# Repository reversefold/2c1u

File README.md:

# 2c1u - Two computers, one USB port

The name is a riff on 2p1c, a shorthand for "Two players, one controller", a fun challenge that some speedrunners enjoy.

This project has software and hardware designs which form a USB switch, allowing for automatically moving a USB device between two computers, either through pressing of a hardware button or controlled via software running on the computers. If you plug a USB hub into the port that is switched you can switch, for instance, a keyboard and mouse between two computers, as if you were using software like Synergy.

## Layout
* 2c1u_kicad - KiCAD files for the hardware of the project, including a PCB layout.
* CircuitPy_Adafruit - Software for the Raspberry Pi devices that the hardware uses.
* 2c1u, pyproject.toml, pdm.lock - These constitute the computer software which communicate to the hardware over USB-Serial.

## Hardware
Required hardware:
* 2x [Adafruit Feather RP2040](https://www.adafruit.com/product/4884)
* 2x [TinkerBoy USB 2.0 Hub Breakout](https://www.tinkerboy.xyz/product/tinkerboy-usb-hub-4-port-usb-hub-2-0/)
* 3x [Adafruit 4090 - USB-C Breakout](https://www.adafruit.com/product/4090)
* 2x [Omron G6SK-2-DC5 relays](https://www.mouser.com/ProductDetail/Omron-Electronics/G6SK-2-DC5?qs=Mrnyg3lK62HQss%2FMQAyqbw%3D%3D)
* 2x [PN2222A Transistor](https://www.digikey.com/en/products/detail/nte-electronics-inc/PN2222A/11655004)
* 2x [Tactile Button Switch](https://www.adafruit.com/product/367)
* 1x [Sparkfun Cherry MX Switch Breakout](https://www.sparkfun.com/products/13773)
* 1x Cherry MX Compatible Switch
* 1x Keycap
* 2x 1K resistors
* 2x 10K resistors

I am also using several feather breakout boards for additional output as I had them around to play with:
* 1x [NeoPixel FeatherWing](https://www.adafruit.com/product/2945)
* 1x [Adafruit FeatherWing OLED - 128x64](https://www.adafruit.com/product/4650)
* 1x [FeatherWing Tripler Mini Kit](https://www.adafruit.com/product/3417)

You will additionally need PCB mount headers for the various components and either breadboards or a custom PCB (see fully functional PCB in `2c1u_kicad`). Note that the TinkerBoy USB 2.0 Hub Breakout boards are not breadboard compatible, the holes are not uniformly separated and require some creativity to hook up with a breadboard.

All of the soldering for the PCB are through-hole, as are nearly all of the boards. The one exception is the two data pads on the RP2040 boards. These pads connect to the 2 data pins of the USB connector so they can be used to wire up the RP2040 to the TinkerBoy boards as a USB device.

The Raspberry Pi boards are the brains of the switch. Each one connects to one of the computers as a USB serial device as a control channel. The primary one also controls the relays which switch the USB devices between the two computers.

One USB connector is for the input device to switch between the two hosts. I use a simple USB hub and plug both my keyboard and mouse into it, then plug the hub into the switch. The other 2 USB connectors connect to the two host computers. The TinkerBoy boards act as USB hubs, allowing both the RPi boards and the input devices to be connected via one USB connection. Note that this switch supports USB 2.0 only, so it's only really useful for lower bandwidth devices, like HID devices.

The Cherry MX switch allows switching between the two host computers manually. The two small switch buttons next to the USB connectors on the PCB can be held down while plugging in the associated USB cable to have the RPi start up in developer mode, with a repl usb-serial connection and as usb mass storage.

## Device-side software
The device-side software is written in Python for CircuitPy running on an Adafruit device. For the secondary create a file named `secondary` in the root of the drive.

The `boot.py` file turns on the data interface and turns off the repl interface, as well as turns off the ability of the CircuitPy device to be a USB drive. If you want access to the USB drive and repl interface you can pull pin D5 up (the buttons next to the USB connectors on the PCB are for this).

## Computer-side software
The computer-side software is written in Python and uses pdm for dependency management. Once you've installed pdm, change to the project directory, use the command `pdm install` to have pdm install all of the dependencies, then use the command `pdm run python 2c1u/main.py` to start the software. Until you have the right hardware hooked up it will loop with exceptions about not finding the serial interface.

The code near the top that defines `X_EDGE` configures how the edge of the screen is detected for the two machines, one Windows on the right, and one not Windows on the left.

## History

This project is the culmination of years of thinking and tinkering in my free time. For a long time, I have used projects such as x2vnc and Synergy to have the mouse and keyboard of one computer move to another computer's screen over the network, allowing for easy use of multiple computers with their own screens with a single keyboard and mouse. When I started working from home more often I wanted a way to switch between my personal and work computers seamlessly. Synergy did just that for me for a while but there were always caveats. Slowdown on the computers and random network errors would cause the input to lag or disconnect.

When my work computer was forced to have a full tunnel VPN the fully software-based network solution just wouldn't work reliably any more. The classic solution to this was a KVM, a hardware switch meant to move a keyboard, video, and mouse from one computer to another. I had no need for the video part of this, however, and I had trouble finding anything which could be software controlled. I wanted to mimic what I could do with Synergy, moving my mouse to one side of the monitor and have my mouse and keyboard move seamlessly to the other computer's monitor next to it.

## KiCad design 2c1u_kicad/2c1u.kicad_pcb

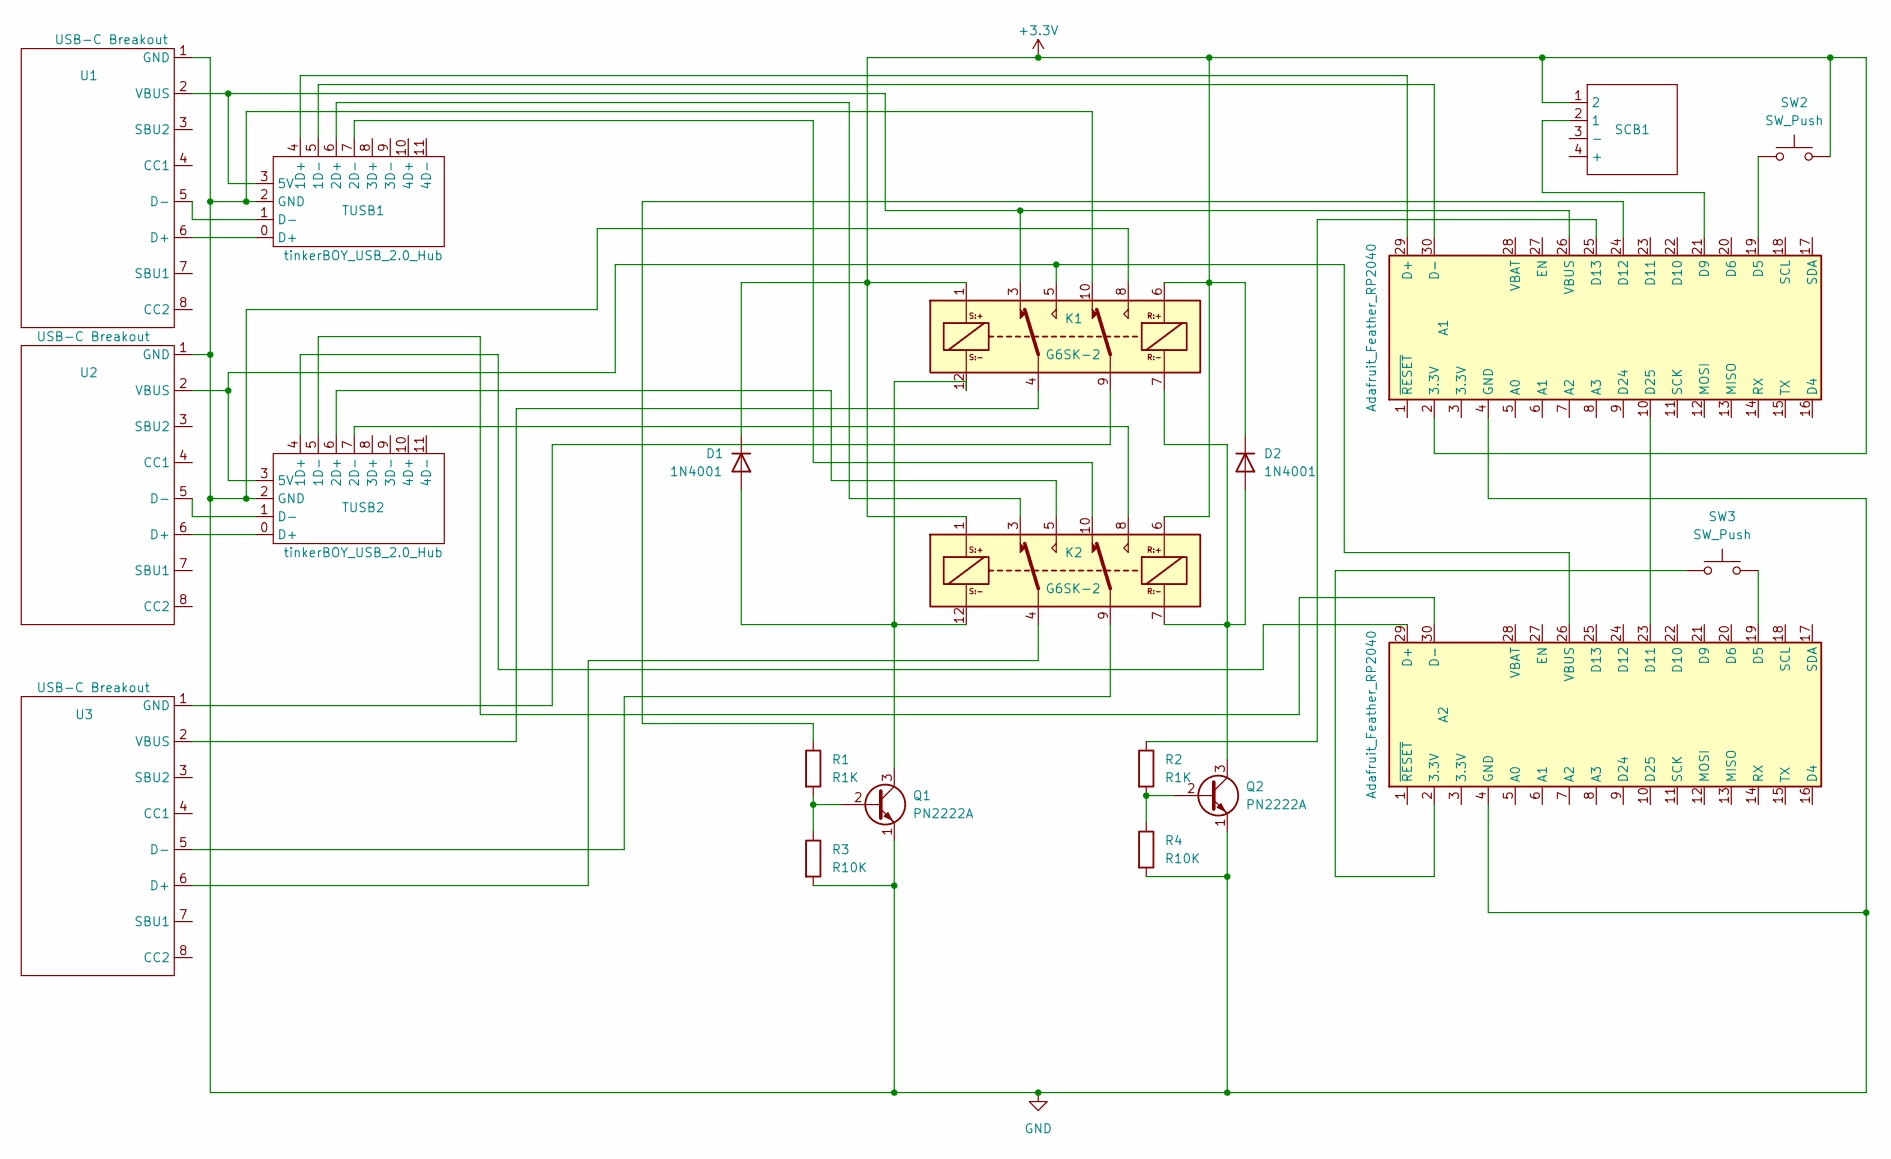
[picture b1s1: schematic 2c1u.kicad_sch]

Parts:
A1, A2: Adafruit_Feather_RP2040; Adafruit Feather RP2040
D1, D2: 1N4001; D_DO-41_SOD81_P10.16mm_Horizontal
K1, K2: G6SK-2; Relay_DPDT_Omron_G6SK-2
Q1, Q2: PN2222A; TO-92_Inline
R1, R2: R1K; R_Axial_DIN0204_L3.6mm_D1.6mm_P5.08mm_Horizontal
R3, R4: R10K; R_Axial_DIN0204_L3.6mm_D1.6mm_P5.08mm_Horizontal
SCB1: (no value)
SW2, SW3: SW_Push; SW_Tactile_Straight_KSL0Axx1LFTR
TUSB1, TUSB2: tinkerBOY_USB_2.0_Hub; tinkerBOY USB 2.0 Hub
U1, U2, U3: USB-C Breakout; Adafruit 4090 - USB-C Breakout

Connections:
+3V3: A1.2 (3.3V), D1.1 (K), D2.1 (K), K1.1, K1.6, K2.1, K2.6, SCB1.1 (2), SW2.2
GND: A1.4 (GND), A2.4 (GND), K1.8, K1.10, Q1.1 (E), Q2.1 (E), R3.2, R4.2, TUSB1.2 (GND), TUSB2.2 (GND), U1.1 (GND), U2.1 (GND)
unnamed: A1.10 (D25), A2.23 (D11)
unnamed: A1.19 (D5), SW2.1
unnamed: A1.24 (D12), R1.1
unnamed: A1.25 (D13), R2.1
unnamed: A1.26 (VBUS), K1.3, TUSB1.3 (5V), U1.2 (VBUS)
unnamed: A1.29 (D+), TUSB1.4 (1D+)
unnamed: A1.30 (D-), TUSB1.5 (1D-)
unnamed: A2.2 (3.3V), SW3.1
unnamed: A2.19 (D5), SW3.2
unnamed: A2.26 (VBUS), K1.5, TUSB2.3 (5V), U2.2 (VBUS)
unnamed: A2.29 (D+), TUSB2.4 (1D+)
unnamed: A2.30 (D-), TUSB2.5 (1D-)
unnamed: D1.2 (A), K1.12, K2.12, Q1.3 (C)
unnamed: D2.2 (A), K1.7, K2.7, Q2.3 (C)
unnamed: K1.4, U3.2 (VBUS)
unnamed: K1.9, U3.1 (GND)
unnamed: K2.3, TUSB1.6 (2D+)
unnamed: K2.4, U3.6 (D+)
unnamed: K2.5, TUSB2.6 (2D+)
unnamed: K2.8, TUSB2.7 (2D-)
unnamed: K2.9, U3.5 (D-)
unnamed: K2.10, TUSB1.7 (2D-)
unnamed: Q1.2 (B), R1.2, R3.1
unnamed: Q2.2 (B), R2.2, R4.1
unnamed: A1.21 (D9), SCB1.2 (1)
unnamed: TUSB1.0 (D+), U1.6 (D+)
unnamed: TUSB1.1 (D-), U1.5 (D-)
unnamed: TUSB2.0 (D+), U2.6 (D+)
unnamed: TUSB2.1 (D-), U2.5 (D-)

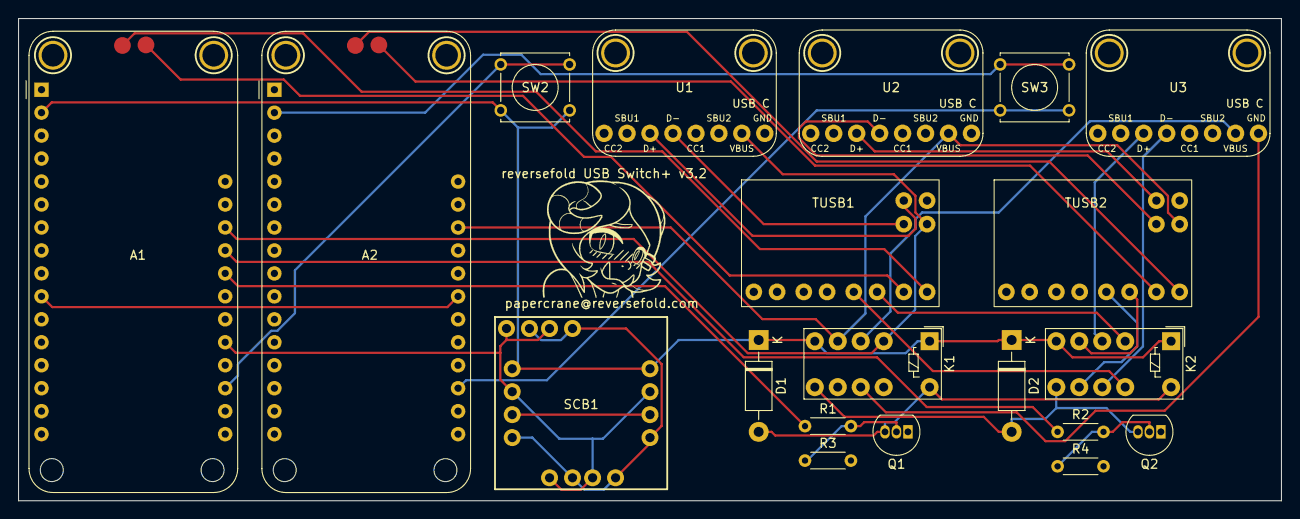
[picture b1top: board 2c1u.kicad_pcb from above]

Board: 2 copper layers, 139.7 x 53.3 mm, 20 parts (0 on the bottom side), 31 nets.

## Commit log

2022-03-24 Initial working version
2022-03-28 Update pins for new layout
2022-03-28 Add rainbow overlay
2022-03-28 Remove CPE code
2022-04-04 Make the pixel screen display an arrow Remove unused CPE code
2022-04-06 Use the data serial device rather than the repl serial device Default to turning off the storage and repl devices with an option to turn them on if a button is held Use adafruit_board_toolkit to find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
2022-04-06 Add KiCAD and gerber files for rev 1.0
2022-04-07 Various updates and fixes * Only GND plane, no 3.3v plane, reduces complexity * Added text for version * Added graphics for fun * Fixed some alignments * Might have fixed some unconnected pads
2022-04-22 Make the color bands move in the direction of the arrow
2022-04-22 Switch to latching relays which allow us to apply current momentarily to switch the relay instead of keeping the current always flowing for one side of the relay
2023-07-23 rfkvm -> 2c1u
2023-07-23 poetry update
2023-07-23 poetry -> pdm
2023-07-23 Remove unneeded code
2023-07-23 Initial README.md
2023-07-23 Add .gitignore
2023-07-24 MAIN and WORK -> PRIMARY and SECONDARY
2023-07-24 Add a BOM with links and a description of the hardware and software
2023-07-24 Fix FeatherWing OLED reference
2023-07-24 Reorder hardware components
2024-01-16 Whitespace
